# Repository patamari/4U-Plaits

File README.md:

# 4U-Plaits
4U port of MI Plaits, "New Digital Oscillator NDO"

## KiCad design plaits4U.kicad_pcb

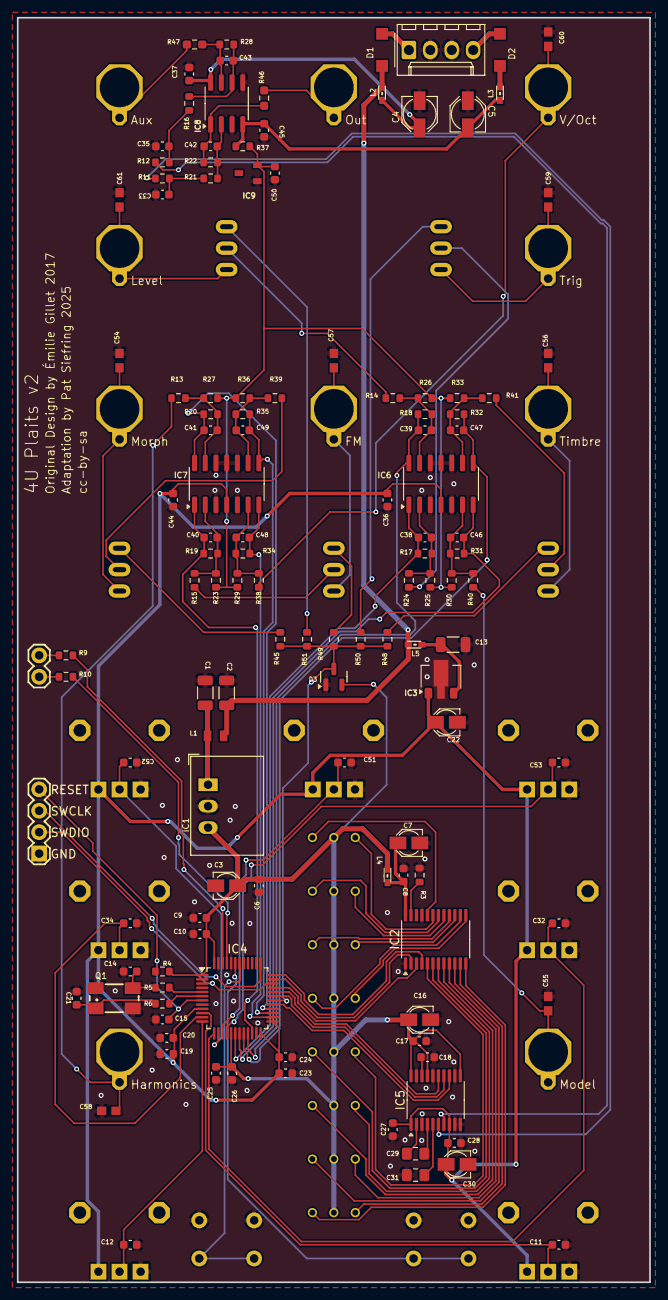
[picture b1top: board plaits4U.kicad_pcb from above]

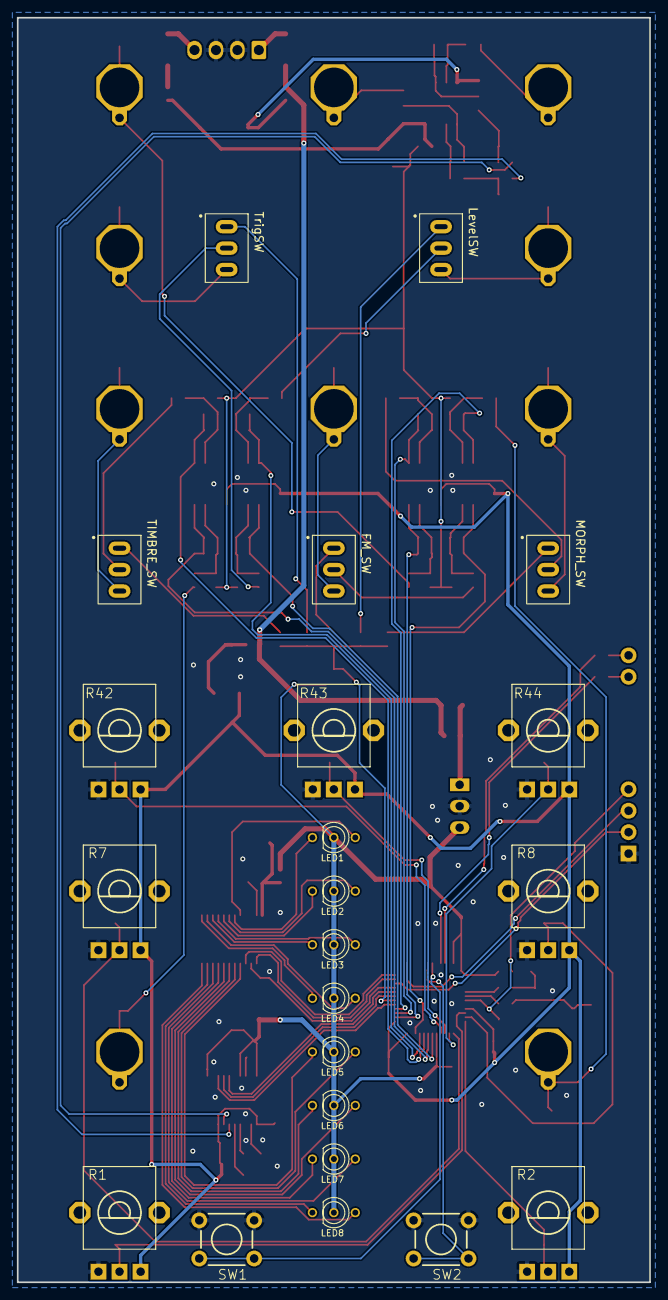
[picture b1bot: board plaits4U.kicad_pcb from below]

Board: 2 copper layers, 74.9 x 149.9 mm, 147 parts (22 on the bottom side), 101 nets.

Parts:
C1, C2, C13: 22u; C_1206_3216Metric
C3, C7, C16, C22, C30: 10u; PANASONIC_A
C4, C5: 22u; PANASONIC_B
C6, C8, C10, C11, C12, C15, C17, C18, C20, C23, C26, C27, C28, C32, C34, C36, C37, C44, C45, C51, C52, C53: 100n; C_0603_1608Metric
C9, C19, C24, C25, C50: 1u; C_0603_1608Metric
C14, C21: 20p; C_0603_1608Metric
C29, C31: 2.2u; C_0805_2012Metric_Pad1.18x1.45mm_HandSolder
C33, C35, C39, C40, C41, C47, C48, C49: 1.0n; C_0603_1608Metric
C38, C42, C43, C46: 100p; C_0603_1608Metric
C54, C55, C56, C57, C58, C59, C60, C61: ESD; C0603
D1, D2: 1N5819HW; SOD123
D3: BAT54S; SOT-23
FM_SW: SubMiniSPDT2.54mm; SubMiniSwitch2.54mm
IC1: R-78E3.3-0.5; Converter_DCDC_RECOM_R-78E-0.5_THT
IC2: TLC59281DBQ; TSSOP-24_4.4x7.8mm_P0.65mm
IC3: LD2981ABU33; SOT-89-3
IC4: STM32F373CCT6; LQFP-48_7x7mm_P0.5mm
IC5: PCM5100APW; SSOP-20_4.4x6.5mm_P0.65mm
IC6, IC7: MCP6004; SOIC-14_3.9x8.7mm_P1.27mm
IC8: TL072PW; SOIC-8_3.9x4.9mm_P1.27mm
IC9: LM4040B10; DBZ_R-PDSO-G3
JP5: 1X02
JP6: 1X04
L1: 33u; L2012C
L2, L3, L4, L5: 0603
LED1, LED2, LED3, LED4, LED5, LED6, LED7, LED8: SSL-LX3059IGW-CA; LED-BICOLOR-THROUGHHOLE-LUMEX
LevelSW: SubMiniSPDT2.54mm; SubMiniSwitch2.54mm
MORPH_SW: SubMiniSPDT2.54mm; SubMiniSwitch2.54mm
Q1: 8MHz; CTS406
R1, R2, R7, R8, R42, R43, R44: 10kB; ALPS_POT_VERTICAL_PS
R3, R4, R16, R21, R45, R48, R49, R50, R51: 10k; R_0603_1608Metric
R5, R6, R9, R10: 100; R_0603_1608Metric
R11, R12, R37: 2.2k; R_0603_1608Metric
R13, R14, R15, R24, R38, R39, R40, R41: 100k; R_0603_1608Metric
R17: 56k; R_0603_1608Metric
R18, R20, R22, R28, R31, R34: 33k; R_0603_1608Metric
R19, R32, R35: 20k; R_0603_1608Metric
R23, R33, R36: 120k; R_0603_1608Metric
R25, R27, R30: 200k; R_0603_1608Metric
R26: 110k; R_0603_1608Metric
R29: 140k; R_0603_1608Metric
R46, R47: 1.0k; R_0603_1608Metric_Pad0.98x0.95mm_HandSolder
SW1, SW2: TACTILE-PTH
TIMBRE_SW: SubMiniSPDT2.54mm; SubMiniSwitch2.54mm
TrigSW: SubMiniSPDT2.54mm; SubMiniSwitch2.54mm

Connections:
+3V3: C3.+, C6.1, C9.1, C10.1, C16.+, C17.1, C25.1, C26.1, D3.2, IC1.3, IC4.1, IC4.17, IC4.48, IC5.11, IC5.17, IC5.20, L4.2, LED1.A, LED2.A, LED3.A, LED4.A, LED5.A, LED6.A, LED7.A, LED8.A, R4.1
+3V3_A: C19.1, C20.1, C22.+, C23.1, C24.1, C27.1, C28.1, C30.+, C36.1, C44.1, IC3.1, IC4.9, IC4.24, IC4.25, IC5.1, IC5.8, IC6.4, IC7.4, R1.P$1, R2.P$1, R7.P$1, R8.P$1, R42.P$1, R43.P$1, R44.P$1
ADC_FM: C40.2, IC4.22, IC7.1, R19.1
ADC_GATE: C39.2, IC4.21, IC6.14, R18.1
ADC_HARMONICS: C41.2, IC4.28, IC7.14, R20.1
ADC_MODEL: C46.2, IC4.19, IC6.7, R31.1
ADC_MORPH: C49.2, IC4.27, IC7.8, R35.1
ADC_TIMBRE: C47.2, IC4.20, IC6.8, R32.1
ADC_TRIG: C38.2, IC4.18, IC6.1, R17.1
ADC_V_OCT: C48.2, IC4.26, IC7.7, R34.1
AREF_-10: C50.1, IC9.2, R23.2, R25.2, R26.2, R27.2, R29.2, R30.2, R33.2, R36.2, R37.2
DAC_BCK: IC4.29, IC5.13
DAC_DIN: IC4.31, IC5.14
DAC_LRCK: IC4.32, IC5.15
FMJack: C57.1, FM_SW.3
FM_IN: FM_SW.2, R15.2
FREQ_ATT: C51.1, IC4.15, R43.P$2
FREQ_POT: C11.1, IC4.10, R1.P$2
GATE_IN: LevelSW.2, R14.2
GATE_IN1: R24.2, TrigSW.2
GND: C1.2, C2.2, C3.-, C4.-, C5.+, C6.2, C7.-, C8.2, C9.2, C10.2, C11.2, C12.2, C13.2, C14.1, C15.2, C16.-, C17.2, C18.2, C19.2, C20.2, C21.1, C22.-, C23.2, C24.2, C25.2, C26.2, C27.2, C28.2, C30.-, C31.2, C32.2, C33.2, C34.2, C35.2, C36.2, C37.2, C44.2, C45.1, C50.2, C51.2, C52.2, C53.2, C54.2, C55.2, C56.2, C57.2, C58.2, C59.2, C60.2, C61.2, D3.1, IC1.2, IC2.1, IC2.21, IC3.2, IC4.8, IC4.23, IC4.44, IC4.47, IC5.3, IC5.9, IC5.10, IC5.12, IC5.16, IC5.19, IC6.3, IC6.5, IC6.10, IC6.11, IC6.12, IC7.3, IC7.5, IC7.10, IC7.11, IC7.12, IC8.3, IC8.5, IC9.1, JP6.1, Q1.2, Q1.4, R1.P$3, R2.P$3, R3.2, R7.P$3, R8.P$3, R42.P$3, R43.P$3, R44.P$3, SW1.1, SW1.2, SW2.1, SW2.2
HARMONICS_IN: C58.1, R13.2
HARMONICS_POT: C12.1, IC4.12, R2.P$2
LEDS_SCK: IC2.3, IC4.33
LEDS_SIN: IC2.2, IC4.35
LEDS_SS: IC2.4, IC4.36
LevelJack: C61.1, LevelSW.3
MODEL_IN: C55.1, R40.2
MORPH_ATT: C52.1, IC4.14, R44.P$2
MORPH_IN: MORPH_SW.2, R39.2
MORPH_POT: C34.1, IC4.11, R8.P$2
MorphJack: C54.1, MORPH_SW.3
unnamed: C1.1, IC1.1, L1.2
unnamed: IC2.12, LED8.GREEN_C
unnamed: R50.2, TrigSW.1
unnamed: C38.1, IC6.2, R17.2, R24.1, R25.1
unnamed: IC2.11, LED8.RED_C
unnamed: C29.1, IC5.2
unnamed: IC4.5, R5.1
unnamed: IC4.6, R6.1
unnamed: IC2.10, LED7.GREEN_C
unnamed: IC2.9, LED7.RED_C
unnamed: IC2.8, LED6.GREEN_C
unnamed: IC2.13, LED4.RED_C
unnamed: IC2.7, LED6.RED_C
unnamed: IC2.14, LED4.GREEN_C
unnamed: IC2.6, LED5.GREEN_C
unnamed: C29.2, IC5.4
unnamed: IC2.15, LED3.RED_C
unnamed: IC2.16, LED3.GREEN_C
unnamed: IC2.17, LED2.RED_C
unnamed: IC2.18, LED2.GREEN_C
unnamed: IC2.19, LED1.RED_C
unnamed: IC2.5, LED5.RED_C
unnamed: IC2.20, LED1.GREEN_C
unnamed: FM_SW.1, R49.1
unnamed: R48.1, TIMBRE_SW.1
unnamed: MORPH_SW.1, R45.1
unnamed: C7.+, C8.1, IC2.24, L4.1
unnamed: C39.1, IC6.13, R14.1, R18.2, R26.1
unnamed: C14.2, Q1.3, R5.2
unnamed: C48.1, IC7.6, R29.1, R34.2, R38.1
unnamed: R41.2, TIMBRE_SW.2
unnamed: C49.1, IC7.9, R35.2, R36.1, R39.1
unnamed: JP5.2, R10.1
unnamed: C40.1, IC7.2, R15.1, R19.2, R23.1
unnamed: C21.2, Q1.1, R6.2
unnamed: LevelSW.1, R51.1
unnamed: C46.1, IC6.6, R30.1, R31.2, R40.1
unnamed: D2.A, L3.2
unnamed: C47.1, IC6.9, R32.2, R33.1, R41.1
unnamed: C2.1, D1.C, L1.1, L2.2, L5.2
unnamed: C41.1, IC7.13, R13.1, R20.2, R27.1
unnamed: C13.1, IC3.3, L5.1
unnamed: IC5.6, R11.2
unnamed: C33.1, R11.1, R21.2
unnamed: C35.1, R12.1, R16.2
unnamed: C31.1, IC5.5
unnamed: JP5.1, R9.1
unnamed: C18.1, IC5.18
unnamed: IC5.7, R12.2
unnamed: C43.1, IC8.6, R16.1, R28.2
unnamed: C43.2, IC8.7, R28.1, R47.2
unnamed: C42.1, IC8.2, R21.1, R22.2
unnamed: C42.2, IC8.1, R22.1, R46.2
unnamed: IC2.23, R3.1
NORMALIZATION_PROBE: D3.3, IC4.30, R45.2, R48.2, R49.2, R50.1, R51.2
RESET: C15.1, IC4.7, JP6.4, R4.2
RX: IC4.46, R9.2
SWCLK: IC4.37, JP6.3
SWDIO: IC4.34, JP6.2
SW_1: IC4.43, SW1.3, SW1.4
SW_2: IC4.42, SW2.3, SW2.4
TIMBRE_ATT: C53.1, IC4.16, R42.P$2
TIMBRE_POT: C32.1, IC4.13, R7.P$2
TX: IC4.45, R10.2
TimbreJack: C56.1, TIMBRE_SW.3
TrigJack: C59.1, TrigSW.3
VCC: C4.+, C37.1, IC8.8, L2.1
VEE: C5.-, C45.2, IC8.4, L3.1, R37.1
V_OCT_IN: C60.1, R38.2

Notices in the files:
plaits4U.kicad_pcb:
cc-by-sa
